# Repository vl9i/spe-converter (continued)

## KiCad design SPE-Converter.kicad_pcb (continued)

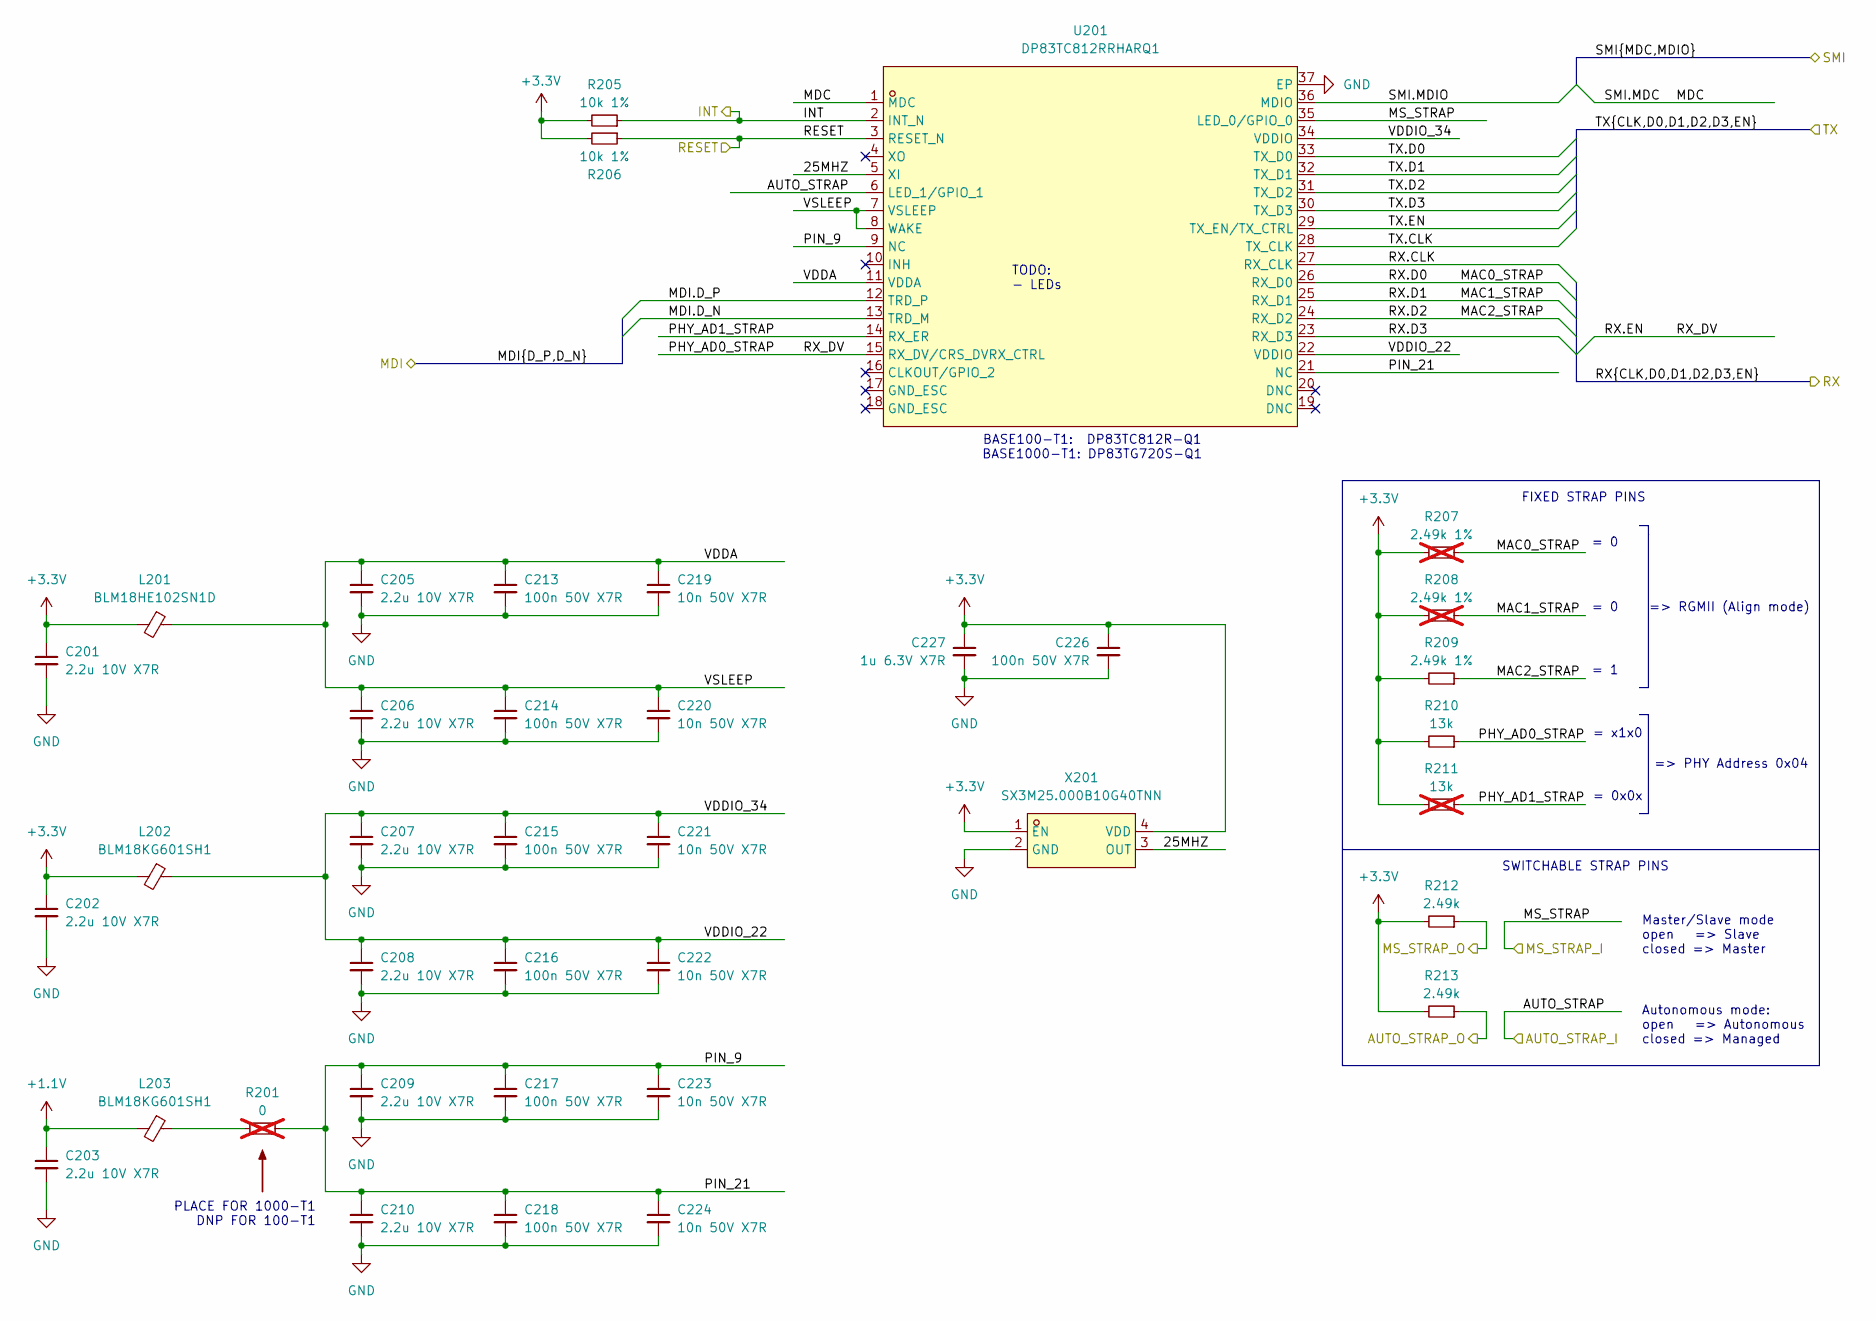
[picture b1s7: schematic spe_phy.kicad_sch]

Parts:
C201, C202, C203, C205, C206, C207, C208, C209, C210: 2.2u 10V X7R; C_0603_1608Metric
C213, C214, C215, C216, C217, C218, C226: 100n 50V X7R; C_0402_1005Metric
C219, C220, C221, C222, C223, C224: 10n 50V X7R; C_0402_1005Metric
C227: 1u 6.3V X7R; C_0402_1005Metric
L201: BLM18HE102SN1D; L_0603_1608Metric; LCSC Part C85828
L202, L203: BLM18KG601SH1; L_0603_1608Metric; LCSC Part C85828
R201: 0; R_0402_1005Metric; not fitted
R205, R206: 10k 1%; R_0402_1005Metric
R207, R208: 2.49k 1%; R_0402_1005Metric; not fitted
R209: 2.49k 1%; R_0402_1005Metric
R210: 13k; R_0402_1005Metric
R211: 13k; R_0402_1005Metric; not fitted
R212, R213: 2.49k; R_0402_1005Metric
U201: DP83TC812RRHARQ1; VQFN-36_L6.0-W6.0-P0.50-TL-EP3.6; LCSC Part C3225810
X201: SX3M25.000B10G40TNN; OSC-SMD_4P-L3.2-W2.5-BL-1; MPN SX3M25.000B10G40TNN; LCSC Part C5452698

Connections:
+1.1V: C203.1, L203.2; also elsewhere on the board
+3.3V: C201.1, C202.1, C226.1, C227.1, L201.2, L202.2, R205.2, R206.2, R207.2, R208.2, R209.2, R210.2, R211.2, R212.2, R213.2, X201.1 (EN), X201.4 (VDD); also elsewhere on the board
/Config/AUTO_STRAP_OUT: R213.1; also elsewhere on the board
/Config/MS_STRAP_OUT: R212.1; also elsewhere on the board
/Ethernet PHY/RX.CLK: U201.28 (TX_CLK); also elsewhere on the board
/Ethernet PHY/RX.D0: U201.33 (TX_D0); also elsewhere on the board
/Ethernet PHY/RX.D1: U201.32 (TX_D1); also elsewhere on the board
/Ethernet PHY/RX.D2: U201.31 (TX_D2); also elsewhere on the board
/Ethernet PHY/RX.D3: U201.30 (TX_D3); also elsewhere on the board
/Ethernet PHY/RX.EN: U201.29 (TX_EN/TX_CTRL); also elsewhere on the board
/Ethernet PHY/SMI.MDC: U201.1 (MDC); also elsewhere on the board
/Ethernet PHY/SMI.MDIO: U201.36 (MDIO); also elsewhere on the board
/Ethernet PHY/TX.CLK: U201.27 (RX_CLK); also elsewhere on the board
/Ethernet PHY/TX.D0: R207.1, U201.26 (RX_D0); also elsewhere on the board
/Ethernet PHY/TX.D1: R208.1, U201.25 (RX_D1); also elsewhere on the board
/Ethernet PHY/TX.D2: R209.1, U201.24 (RX_D2); also elsewhere on the board
/Ethernet PHY/TX.D3: U201.23 (RX_D3); also elsewhere on the board
/Ethernet PHY/TX.EN: R210.1, U201.15 (RX_DV/CRS_DVRX_CTRL); also elsewhere on the board
/SPE Conn/MDI.D_N: U201.13 (TRD_M); also elsewhere on the board
/SPE Conn/MDI.D_P: U201.12 (TRD_P); also elsewhere on the board
/SPE PHY/25MHZ: U201.5 (XI), X201.3 (OUT)
/SPE PHY/AUTO_STRAP: U201.6 (LED_1/GPIO_1); also elsewhere on the board
/SPE PHY/INT: R205.1, U201.2 (INT_N); also elsewhere on the board
/SPE PHY/MS_STRAP: U201.35 (LED_0/GPIO_0); also elsewhere on the board
/SPE PHY/PHY_AD1_STRAP: R211.1, U201.14 (RX_ER)
/SPE PHY/PIN_21: C209.1, C210.1, C217.1, C218.1, C223.1, C224.1, R201.1, U201.9 (NC), U201.21 (NC)
/SPE PHY/RESET: R206.1, U201.3 (RESET_N); also elsewhere on the board
/SPE PHY/VDDA: C205.1, C206.1, C213.1, C214.1, C219.1, C220.1, L201.1, U201.7 (VSLEEP), U201.8 (WAKE), U201.11 (VDDA)
/SPE PHY/VDDIO_22: C207.1, C208.1, C215.1, C216.1, C221.1, C222.1, L202.1, U201.22 (VDDIO), U201.34 (VDDIO)
GND: C201.2, C202.2, C203.2, C205.2, C206.2, C207.2, C208.2, C209.2, C210.2, C213.2, C214.2, C215.2, C216.2, C217.2, C218.2, C219.2, C220.2, C221.2, C222.2, C223.2, C224.2, C226.2, C227.2, U201.37 (EP), X201.2 (GND); also elsewhere on the board
unnamed: L203.1, R201.2

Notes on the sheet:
= 0
FIXED STRAP PINS
= 0x0x
= x1x0
BASE100-T1: DP83TC812R-Q1 BASE1000-T1: DP83TG720S-Q1
Autonomous mode: open => Autonomous closed => Managed
=> PHY Address 0x04
PLACE FOR 1000-T1 DNP FOR 100-T1
Master/Slave mode open => Slave closed => Master
=> RGMII (Align mode)
TODO: - LEDs
= 1
SWITCHABLE STRAP PINS

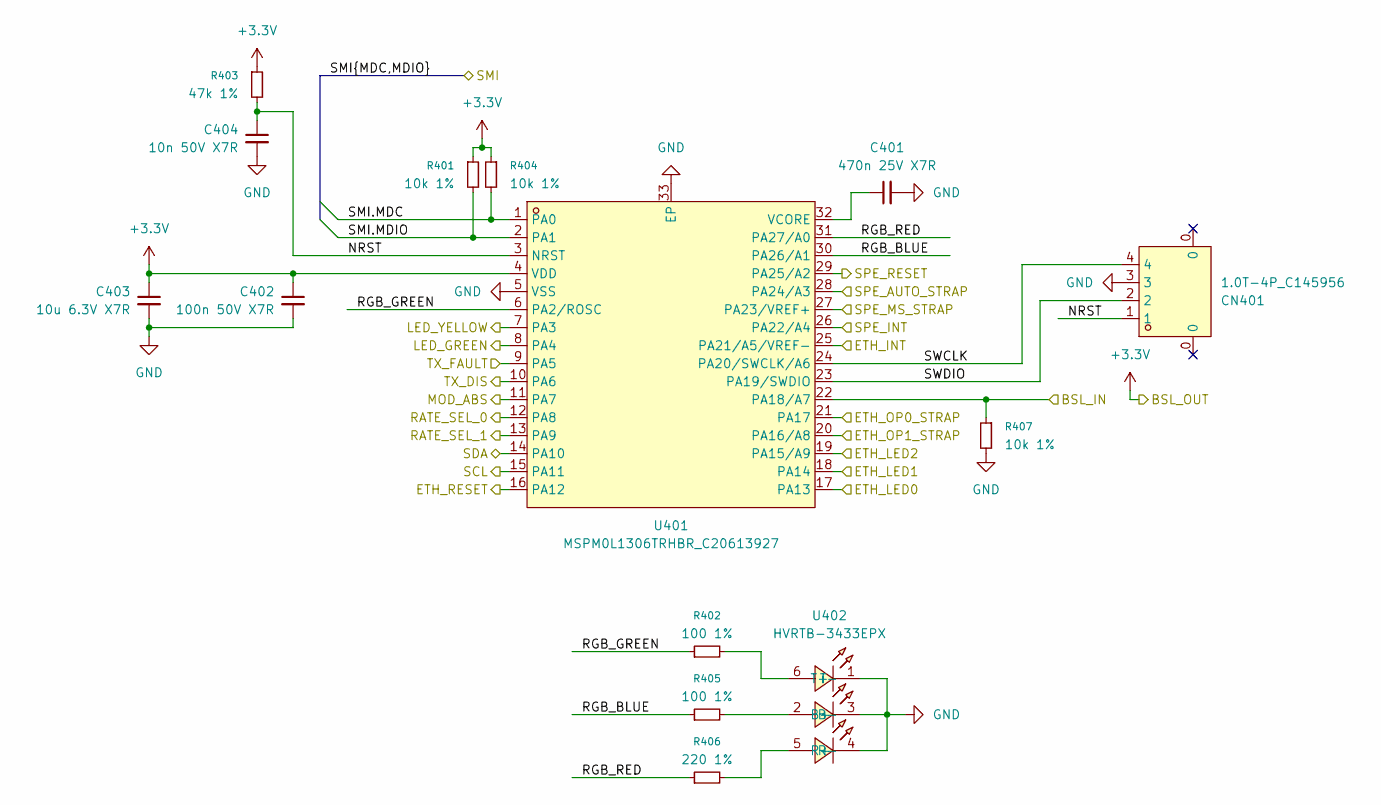
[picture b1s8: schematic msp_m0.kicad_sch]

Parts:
C401: 470n 25V X7R; C_0603_1608Metric
C402: 100n 50V X7R; C_0402_1005Metric
C403: 10u 6.3V X7R; C_0603_1608Metric
C404: 10n 50V X7R; C_0402_1005Metric
CN401: 1.0T-4P_C145956; CONN-SMD_1.0T-4P; MPN 1.0T-4P卧贴; LCSC Part C145956
R401, R404, R407: 10k 1%; R_0402_1005Metric
R402, R405: 100 1%; R_0402_1005Metric
R403: 47k 1%; R_0402_1005Metric
R406: 220 1%; R_0402_1005Metric
U401: MSPM0L1306TRHBR_C20613927; VQFN-32_L5.0-W5.0-P0.50-TL-EP3.5; MPN MSPM0L1306TRHBR; LCSC Part C20613927
U402: HVRTB-3433EPX; LED-SMD_6P-L3.4-W3.4-P1.10_HVRTB-3433EPX; LCSC Part C5246356

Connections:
+3.3V: C402.1, C403.1, R401.1, R403.1, R404.1, U401.4 (VDD); also elsewhere on the board
/Config/BSL_IN: R407.1, U401.22 (PA18/A7); also elsewhere on the board
/Config/OP1_STRAP_IN: U401.20 (PA16/A8); also elsewhere on the board
/Ethernet PHY/INT: U401.25 (PA21/A5/VREF-); also elsewhere on the board
/Ethernet PHY/LED0_STRAP: U401.17 (PA13); also elsewhere on the board
/Ethernet PHY/LED1_STRAP: U401.18 (PA14); also elsewhere on the board
/Ethernet PHY/LED2_STRAP: U401.19 (PA15/A9); also elsewhere on the board
/Ethernet PHY/OP0_STRAP: U401.21 (PA17); also elsewhere on the board
/Ethernet PHY/RESET: U401.16 (PA12); also elsewhere on the board
/Ethernet PHY/SMI.MDC: R404.2, U401.1 (PA0); also elsewhere on the board
/Ethernet PHY/SMI.MDIO: R401.2, U401.2 (PA1); also elsewhere on the board
/MSP M0/LED_GREEN: U401.8 (PA4); also elsewhere on the board
/MSP M0/LED_YELLOW: U401.7 (PA3); also elsewhere on the board
/MSP M0/MOD_ABS: U401.11 (PA7); also elsewhere on the board
/MSP M0/NRST: C404.1, CN401.1, R403.2, U401.3 (NRST)
/MSP M0/RATE_SEL_0: U401.12 (PA8); also elsewhere on the board
/MSP M0/RATE_SEL_1: U401.13 (PA9); also elsewhere on the board
/MSP M0/RGB_BLUE: R405.1, U401.30 (PA26/A1)
/MSP M0/RGB_GREEN: R402.1, U401.6 (PA2/ROSC)
/MSP M0/RGB_RED: R406.1, U401.31 (PA27/A0)
/MSP M0/SCL: U401.15 (PA11); also elsewhere on the board
/MSP M0/SDA: U401.14 (PA10); also elsewhere on the board
/MSP M0/SWCLK: CN401.4, U401.24 (PA20/SWCLK/A6)
/MSP M0/SWDIO: CN401.2, U401.23 (PA19/SWDIO)
/MSP M0/TX_DIS: U401.10 (PA6); also elsewhere on the board
/MSP M0/TX_FAULT: U401.9 (PA5); also elsewhere on the board
/SPE PHY/AUTO_STRAP: U401.28 (PA24/A3); also elsewhere on the board
/SPE PHY/INT: U401.26 (PA22/A4); also elsewhere on the board
/SPE PHY/MS_STRAP: U401.27 (PA23/VREF+); also elsewhere on the board
/SPE PHY/RESET: U401.29 (PA25/A2); also elsewhere on the board
GND: C401.2, C402.2, C403.2, C404.2, CN401.3, R407.2, U401.5 (VSS), U401.33 (EP), U402.1 (T-), U402.3 (B-), U402.4 (R-); also elsewhere on the board
unnamed: C401.1, U401.32 (VCORE)
unnamed: R405.2, U402.2 (B+)
unnamed: R406.2, U402.5 (R+)
unnamed: R402.2, U402.6 (T+)

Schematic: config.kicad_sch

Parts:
SW902: SMWA-08B-TP; SW-TH_16P-L21.9-W6.2-P2.54-LS2.54; MPN SMWA-08B-TP; LCSC Part C5299542

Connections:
+3.3V: SW902.10, SW902.11, SW902.13, SW902.15; also elsewhere on the board
/Config/AUTO_STRAP_OUT: SW902.12; also elsewhere on the board
/Config/BSL_IN: SW902.6; also elsewhere on the board
/Config/MS_STRAP_OUT: SW902.14; also elsewhere on the board
/Config/OP0_STRAP_OUT: SW902.9; also elsewhere on the board
/Config/OP1_STRAP_IN: SW902.7; also elsewhere on the board
/Config/SPE_MUX_EN_IN: SW902.2; also elsewhere on the board
/Config/SPE_MUX_PORT_IN: SW902.4; also elsewhere on the board
/Ethernet PHY/OP0_STRAP: SW902.8; also elsewhere on the board
/SPE PHY/AUTO_STRAP: SW902.5; also elsewhere on the board
/SPE PHY/MS_STRAP: SW902.3; also elsewhere on the board

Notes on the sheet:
BASE100-T1: SMWA-08B-TP BASE1000-T1: DA-08RP

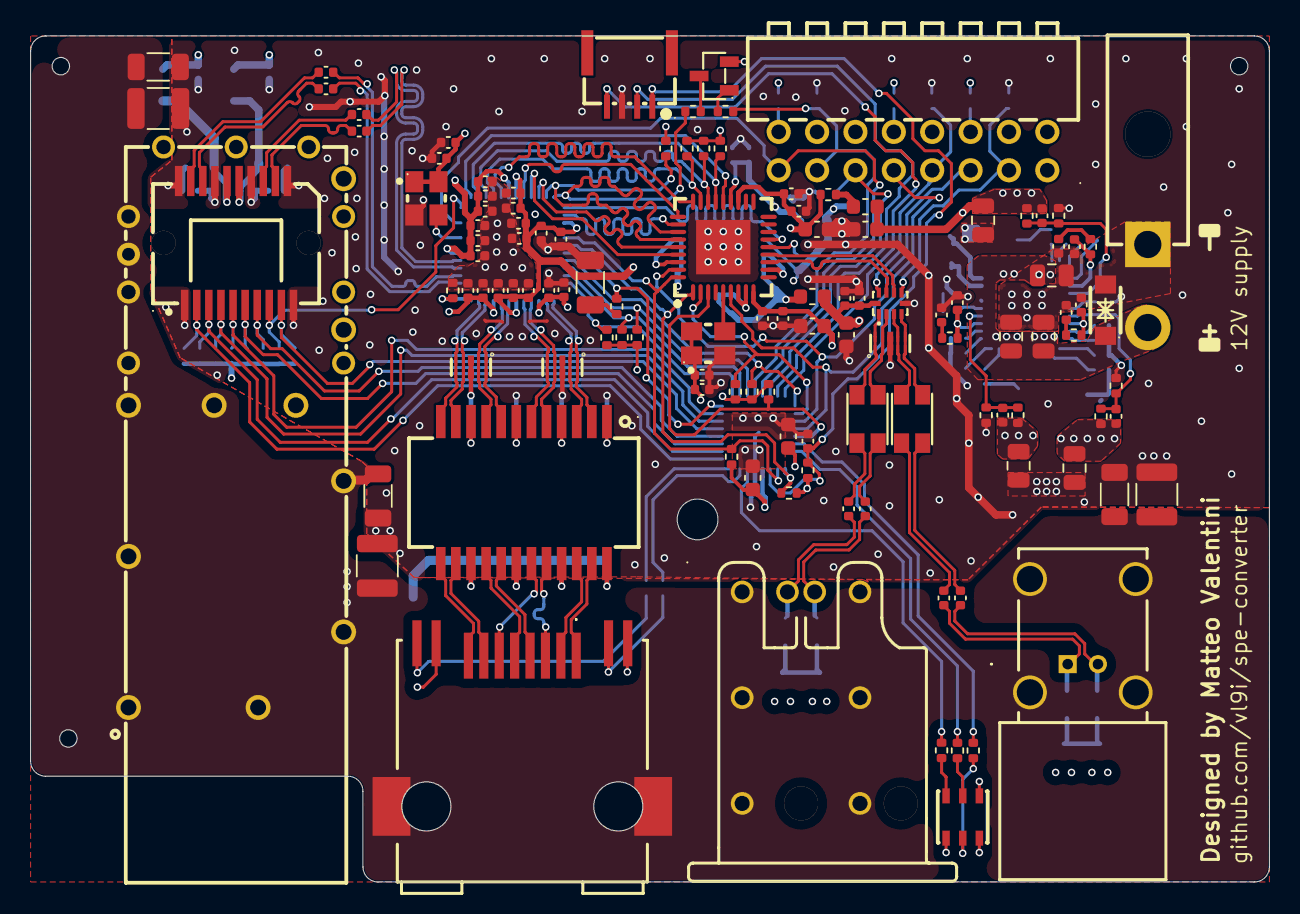
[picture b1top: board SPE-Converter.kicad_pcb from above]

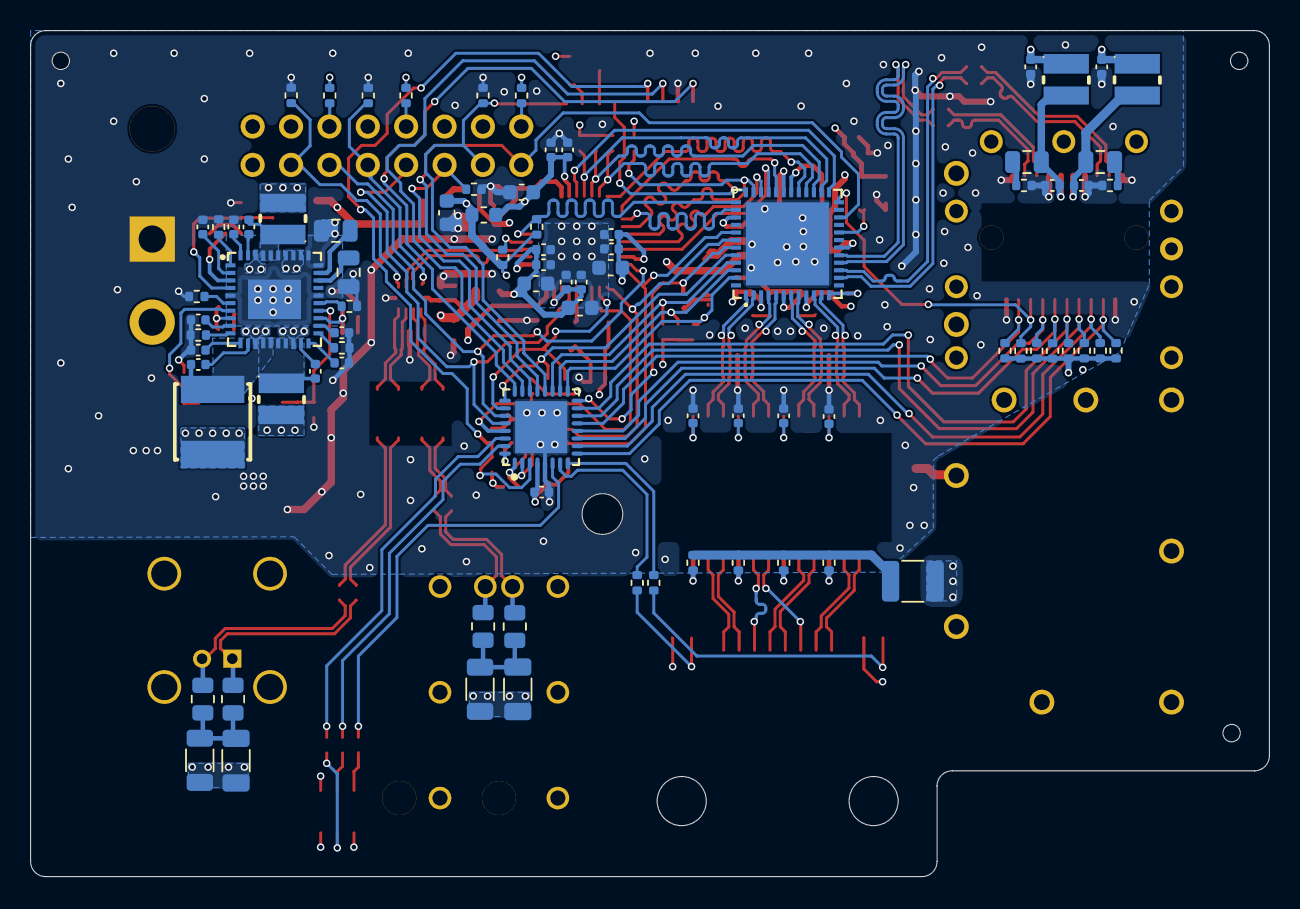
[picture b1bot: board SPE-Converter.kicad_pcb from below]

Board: 4 copper layers, 81.8 x 55.9 mm, 206 parts (83 on the bottom side), 151 nets.

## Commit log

2026-06-28 not fully done yet
2026-06-29 finially done
